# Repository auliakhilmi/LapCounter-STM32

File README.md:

# LapCounter-STM32
Lap Counter using STM32

#### Version 1 STM32F103 
#### Version 2 STM32F407-Discovery

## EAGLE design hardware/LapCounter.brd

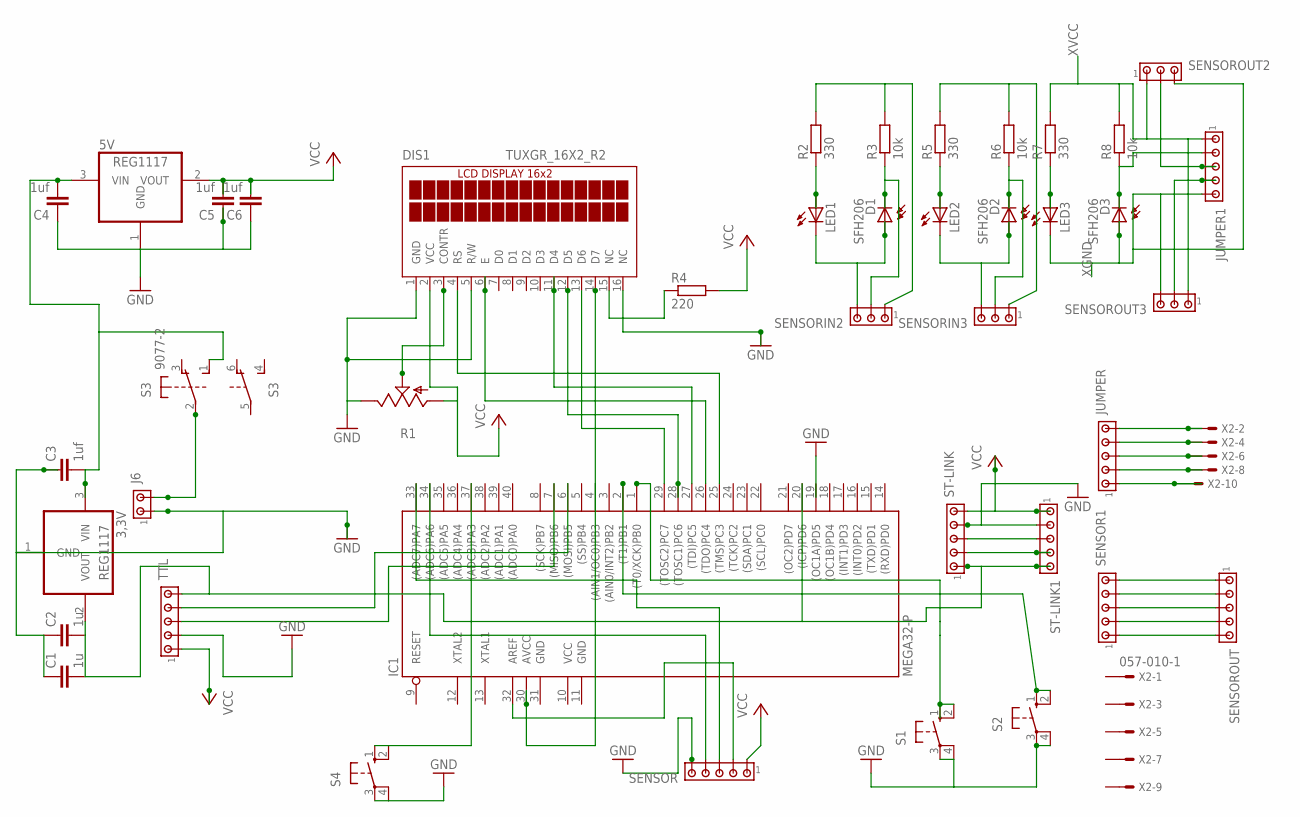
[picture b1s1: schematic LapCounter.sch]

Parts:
3,3V, 5V: REG1117; SOT223
C1, C2: 1u; C0805
C3, C4, C5, C6: 1uf; C0805
D1, D2, D3: SFH206
DIS1: TUXGR_16X2_R2
IC1: MEGA32-P; DIL40
J6: MTA02-100; 10X02MTA
JUMPER, JUMPER1: MTA05-100; 10X05MTA
LED1, LED2, LED3: LED5MM
R1: TRIM_US-CA6V; CA6V
R2, R5, R7: 330; M1206
R3, R6, R8: 10k; M1206
R4: 220; M1206
S1, S2, S4: 40-XX; B3F-40XX
S3: 9077-2
SENSOR, SENSOR1: MTA05-100; 10X05MTA
SENSORIN2, SENSORIN3: MTA03-100; 10X03MTA
SENSOROUT: MTA05-100; 10X05MTA
SENSOROUT2, SENSOROUT3: MTA03-100; 10X03MTA
ST-LINK, ST-LINK1: MTA05-100; 10X05MTA
TTL: MTA05-100; 10X05MTA
X2: 057-010-1

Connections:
5V: J6.2, S3.2
GND: 3,3V.1 (GND), 5V.1 (GND), C1.1, C2.1, C3.1, C4.1, C5.1, C6.1, DIS1.1 (GND), DIS1.5 (R/W), DIS1.16 (NC), IC1.11 (GND), IC1.31 (GND), J6.1, R1.E, S1.3, S1.4 (P1), S2.3, S2.4 (P1), S4.3, S4.4 (P1), SENSOR.5, ST-LINK.4, ST-LINK1.2, TTL.2
unnamed: DIS1.4 (RS), IC1.25 ((TMS)PC3)
unnamed: SENSOR1.5, SENSOROUT.1
unnamed: DIS1.3 (CONTR), R1.S
unnamed: ST-LINK.2, ST-LINK1.4
unnamed: DIS1.15 (NC), R4.1
unnamed: DIS1.6 (E), IC1.26 ((TDO)PC4)
unnamed: DIS1.11 (D4), IC1.27 ((TDI)PC5)
unnamed: DIS1.12 (D5), IC1.28 ((TOSC1)PC6)
unnamed: DIS1.13 (D6), IC1.29 ((TOSC2)PC7)
unnamed: DIS1.14 (D7), IC1.30 (AVCC)
unnamed: ST-LINK.3, ST-LINK1.3
unnamed: 3,3V.3 (VIN), 5V.3 (VIN), C3.2, C4.2, S3.1 (S)
unnamed: JUMPER.5, X2.2
unnamed: JUMPER.4, X2.4
unnamed: IC1.7 ((MISO)PB6), TTL.3
unnamed: IC1.37 ((ADC3)PA3), S4.1 (S), S4.2 (S1)
unnamed: IC1.33 ((ADC7)PA7), SENSOR.3
unnamed: IC1.32 (AREF), SENSOR.2
unnamed: IC1.34 ((ADC6)PA6), SENSOR.4
unnamed: SENSOR1.4, SENSOROUT.2
unnamed: SENSOR1.3, SENSOROUT.3
unnamed: JUMPER.3, X2.6
unnamed: JUMPER.2, X2.8
unnamed: IC1.6 ((MOSI)PB5), TTL.4
unnamed: SENSOR1.2, SENSOROUT.4
unnamed: JUMPER.1, X2.10
unnamed: IC1.1 ((T0/XCK)PB0), S1.1 (S), S1.2 (S1)
unnamed: IC1.2 ((T1)PB1), S2.1 (S), S2.2 (S1)
unnamed: 3,3V.2 (VOUT), C1.2, C2.2, IC1.20 ((ICP)PD6), ST-LINK.1, ST-LINK1.5, TTL.5
unnamed: SENSOR1.1, SENSOROUT.5
unnamed: D1.A, LED1.K (C), SENSORIN2.3
unnamed: LED1.A, R2.1
unnamed: D1.K (C), R3.1, SENSORIN2.2
unnamed: R2.2, R3.2, SENSORIN2.1
unnamed: D2.A, LED2.K (C), SENSORIN3.3
unnamed: LED2.A, R5.1
unnamed: D2.K (C), R6.1, SENSORIN3.2
unnamed: R5.2, R6.2, SENSORIN3.1
unnamed: LED3.A, R7.1
unnamed: D3.K (C), JUMPER1.2, R8.1
unnamed: JUMPER1.4, SENSOROUT3.2
unnamed: JUMPER1.3, SENSOROUT2.2
VCC: 5V.2 (VOUT), C5.2, C6.2, DIS1.2 (VCC), IC1.10 (VCC), R1.A, R4.2, SENSOR.1, ST-LINK.5, ST-LINK1.1, TTL.1
XGND: D3.A, JUMPER1.5, LED3.K (C), SENSOROUT2.3, SENSOROUT3.3
XVCC: JUMPER1.1, R7.2, R8.2, SENSOROUT2.1, SENSOROUT3.1

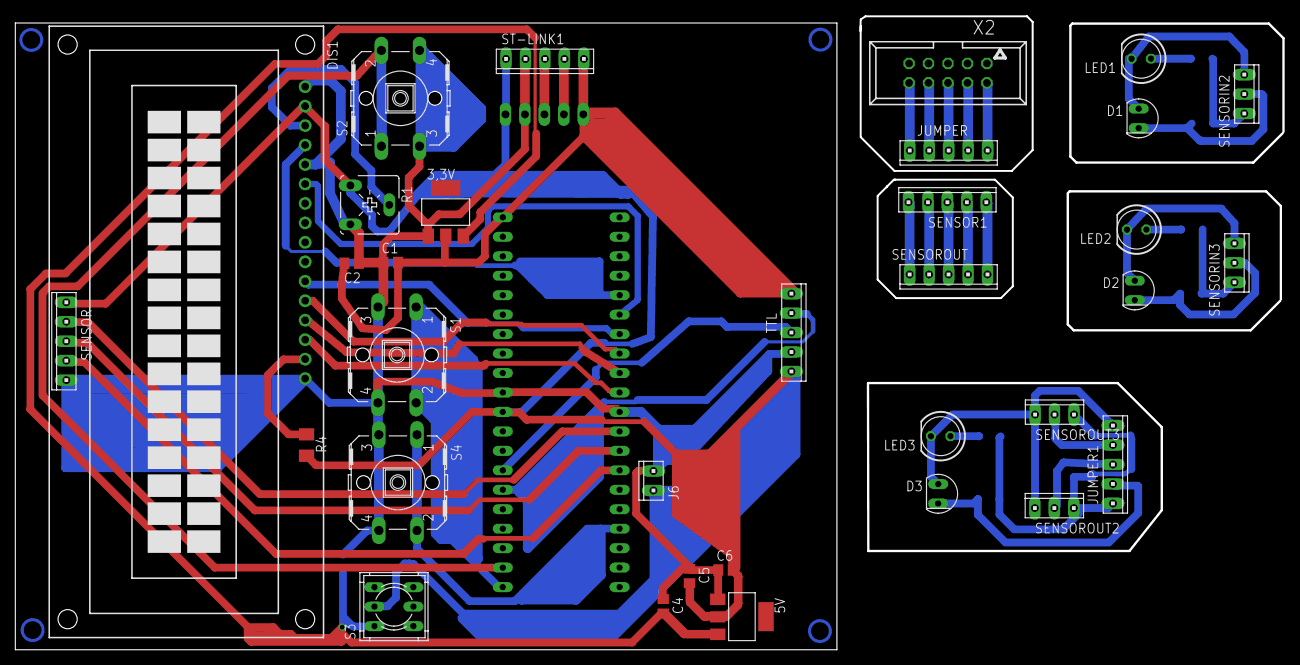
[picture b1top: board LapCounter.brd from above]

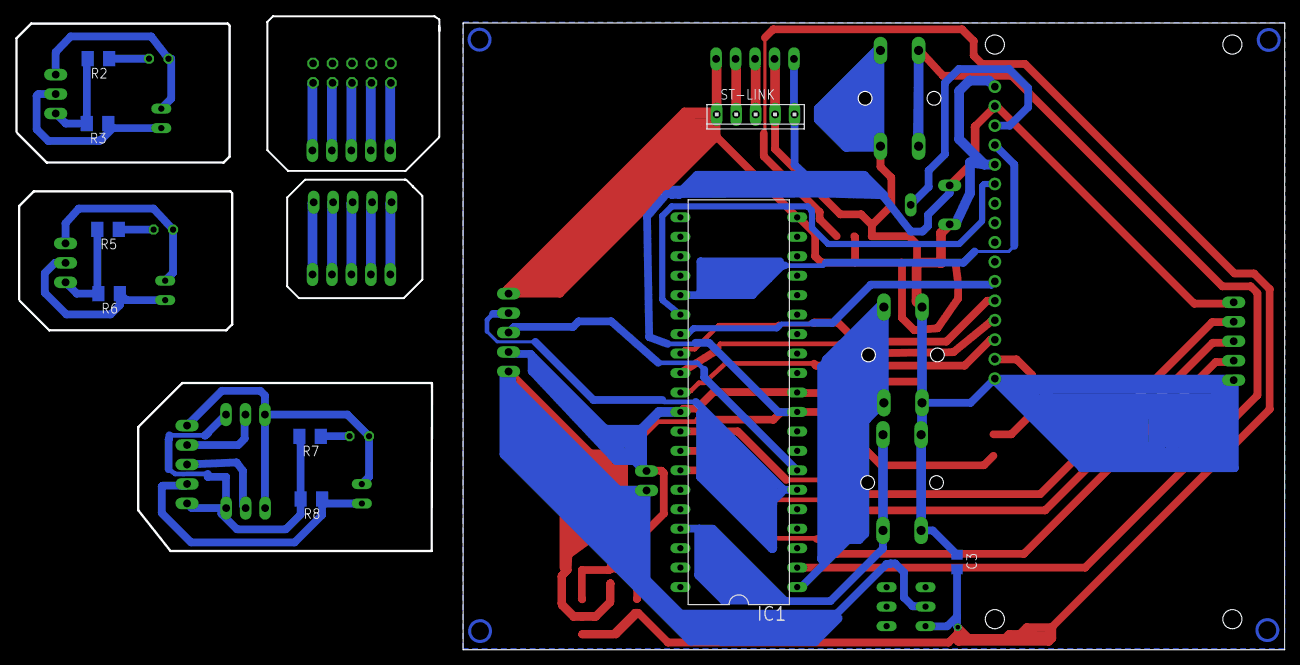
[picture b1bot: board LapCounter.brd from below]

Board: 2 copper layers, 165.4 x 82.5 mm, 42 parts (9 on the bottom side), 47 nets.

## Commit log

2017-11-29 Create test
